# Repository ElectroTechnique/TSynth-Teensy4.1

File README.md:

# Teensy 4.1 based synthesizer using PJRC Audio Board and Audio Lib

Website: [electrotechnique.cc](https://electrotechnique.cc)

Front panel and Main PCB files are now available if you wan to get your own from a PCB facility like JLCPCB.

~~The pcb and front panel to build TSynth are available from [Tindie](https://www.tindie.com/products/electrotechnique/tsynth-teensy-based-diy-programmable-poly-synth/) with SMD 4067 multiplexers, 6N137 opto-isolator, capacitors and resistors fitted.~~ 

The entire cost of parts to build TSynth will be around $99 if you buy components from the cheaper suppliers and the build time around two hours to solder.
Plans for a 3D printed/laser cut enclosure are also available.

Questions: info@electrotechnique.cc

# Preset Patches
Format your SD card using [the SD Association formatter](https://www.sdcard.org/downloads/formatter/). Copy all the presets straight on to the card with no other files or folders.

# Instructions

The source code **requires** the latest Teensyduino from [PJRC](https://pjrc.com) to compile. You also need CircularBuffer from Agileware and Adafruit_GFX, which are available in the Arduino Library Manager.

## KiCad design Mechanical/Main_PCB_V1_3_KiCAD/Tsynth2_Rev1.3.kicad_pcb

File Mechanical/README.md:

- Electrical schematic
- 3D models - End cheeks, side panel columns, display standoff, encoder knob (D-shape shaft)

    EncoderKnobEC12_6mm is for 6mm splined encoder shafts
    
    EncoderKnobEC12_D_shape is for 6mm D-shaped encoder shafts

- Laser cutter plans - Sides and base

    T4_1_LaserCutCase3_5Jk.svg - Is for PCBs with 3.5mm headphone sockets
  
    T4_1_LaserCutCase6_35Jk.svg - Is for PCBs with 1/4" / 6.35mm headphone sockets
  
- BOM Excel file for ordering from Mouser

Fusion 360 models. These have internal dimensions for slots that are slightly bigger, to account for shrinkage of PLA plastic:
- [End Cheeks](https://a360.co/3azEESA)
- [Side Panel Column](https://a360.co/34T8akU)

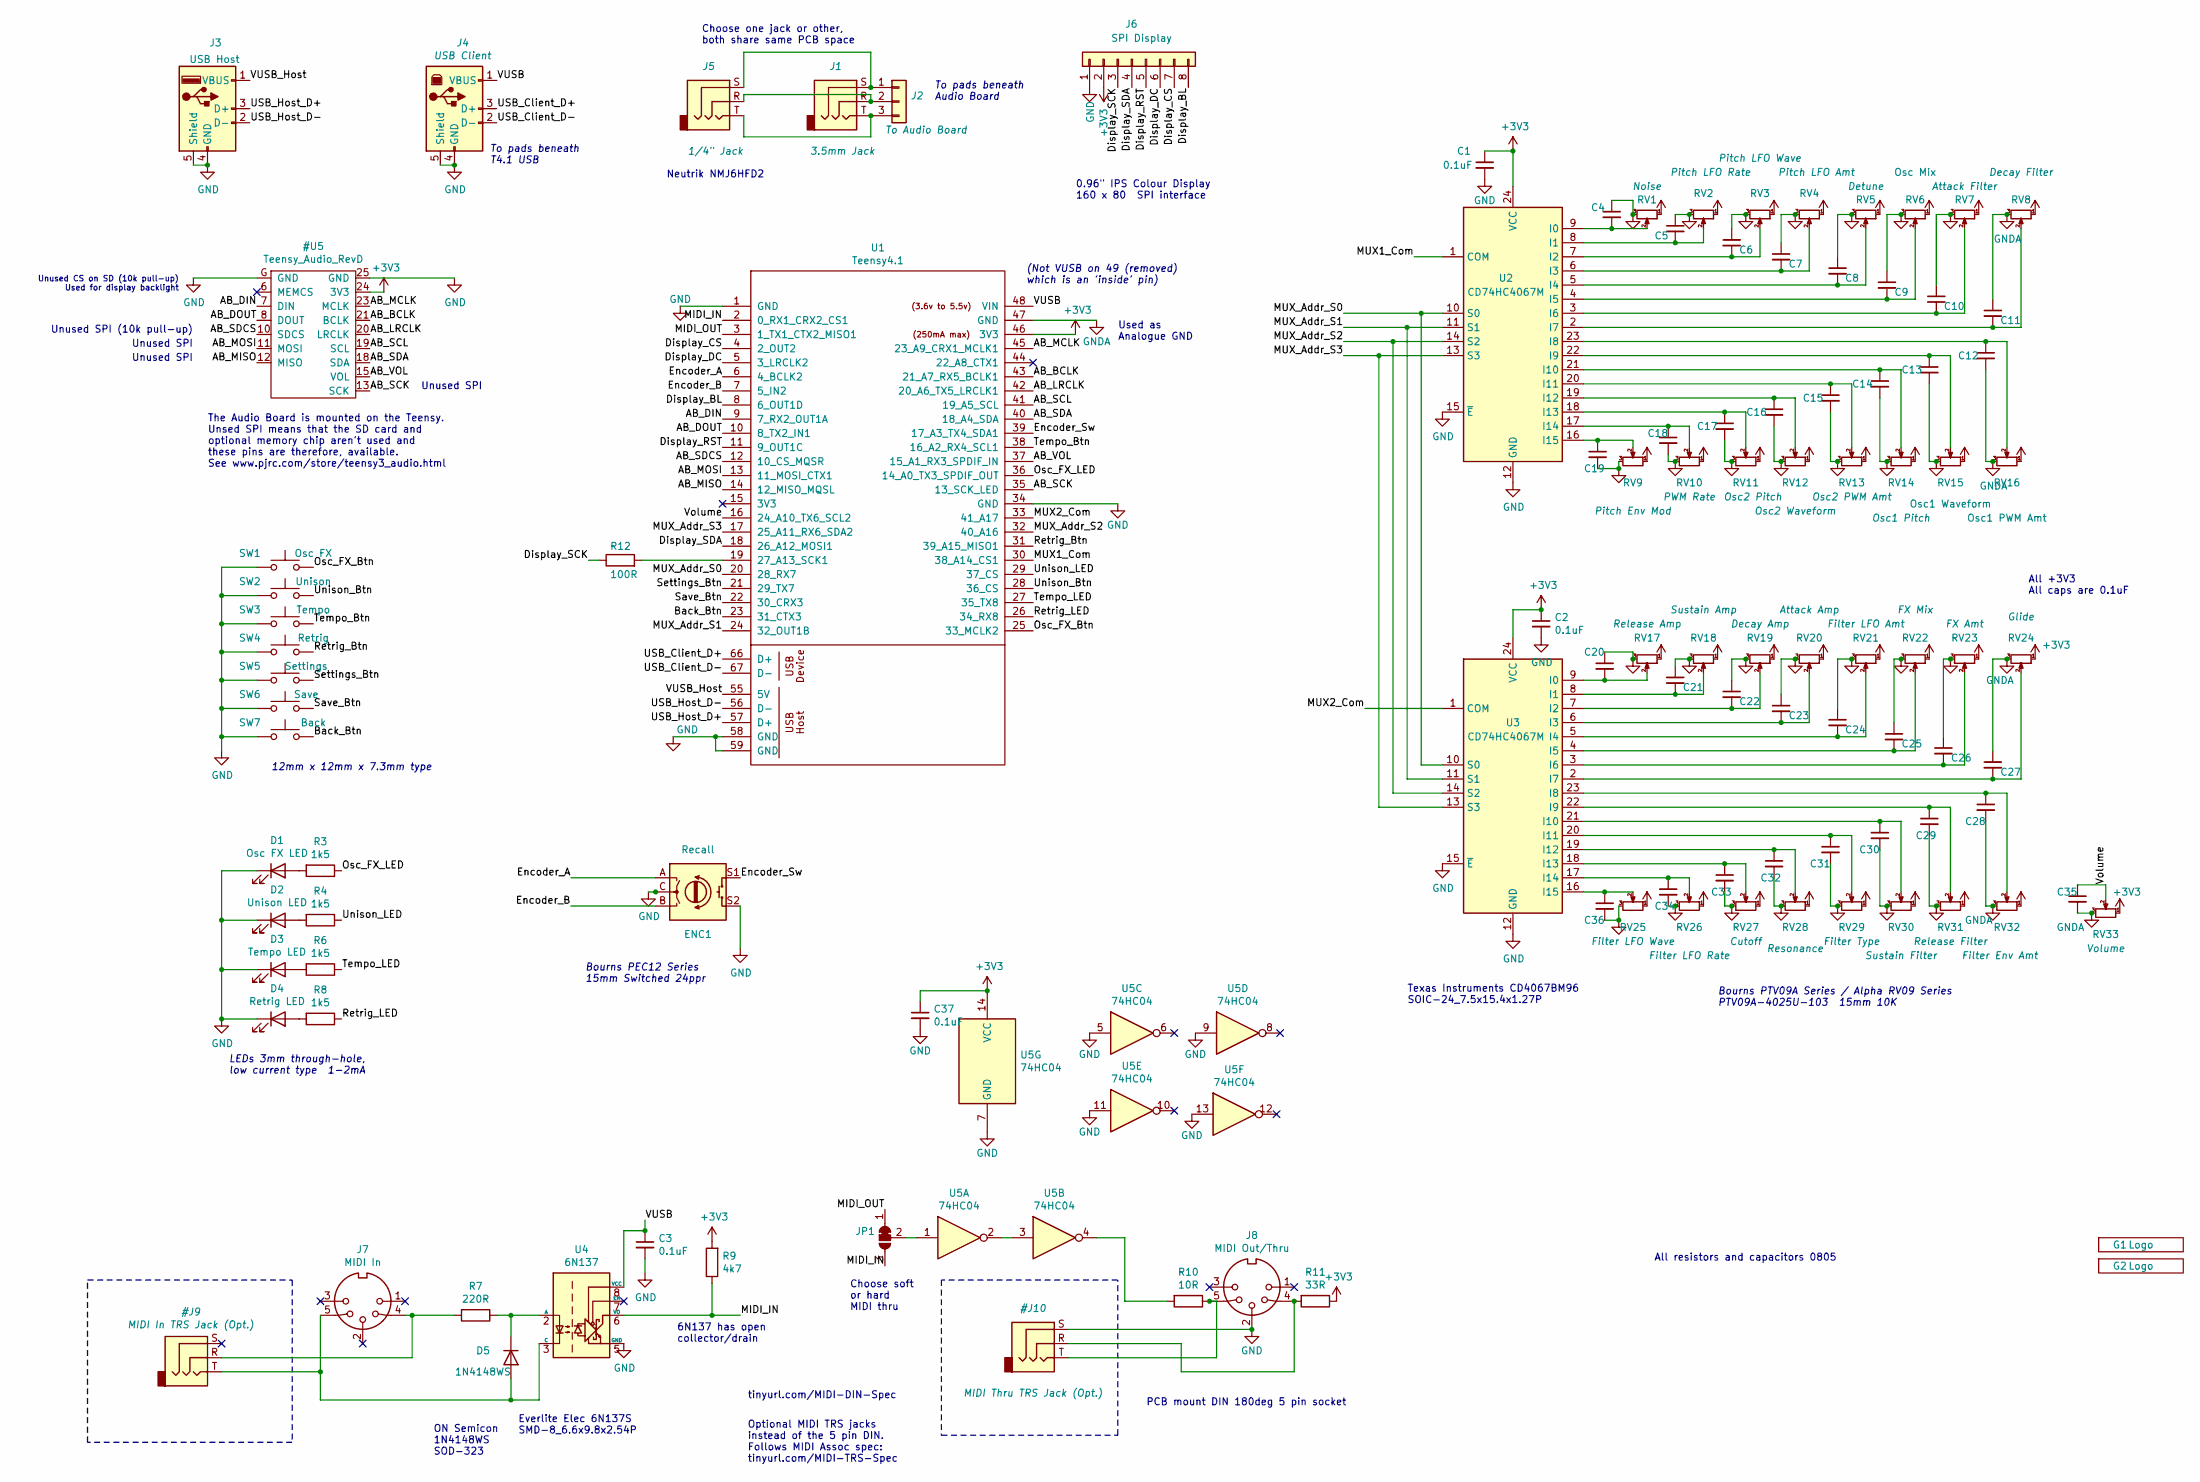
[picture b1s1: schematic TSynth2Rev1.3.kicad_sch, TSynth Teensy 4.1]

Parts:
C1, C37: 0.1uF; R_0805_2012Metric; LCSC C49678
C2, C3, C4, C5, C6, C7, C8, C9, C10, C11, C12, C13, C14, C15, C16, C17, C18, C19, C20, C21, C22, C23, C24, C25, C26, C27, C28, C29, C30, C31, C32, C33, C34, C35, C36: 0.1uF; R_0805_2012Metric
D1: Osc FX LED; LED_D3.0mm
D2: Unison LED; LED_D3.0mm
D3: Tempo LED; LED_D3.0mm
D4: Retrig LED; LED_D3.0mm
D5: 1N4148WS; D_SOD-323F; LCSC C2128
ENC1: Recall; RotaryEncoder_Alps_EC11E-Switch_Vertical_H20mm
G1, G2: Logo; TSynth PCB Logo 41mm
J1: 3.5mm Jack; Jack_3.5mm_Ledino_KB3SPRS_Horizontal
J2: To Audio Board; PinHeader_1x03_P2.54mm_Vertical
J3: USB Host; USB_A_Stewart_SS-52100-001_Horizontal
J4: USB Client; USB_B_OST_USB-B1HSxx_Horizontal
J5: 1/4" Jack; Jack_6.35mm_Neutrik_NMJ6HFD2_Horizontal
J6: SPI Display; PinHeader_1x08_P2.54mm_Vertical
J7: MIDI In; MIDI_DIN5
J8: MIDI Out/Thru; MIDI_DIN5
JP1: SolderJumper_3_Bridged12; SolderJumper-3_P1.3mm_Bridged12_RoundedPad1.0x1.5mm
R3, R4, R6, R8: 1k5; R_0805_2012Metric; LCSC C4310
R7: 220R; R_0805_2012Metric; LCSC C17557
R9: 4k7; R_0805_2012Metric; LCSC C17673
R10: 10R; R_0805_2012Metric; LCSC C17415
R11: 33R; R_0805_2012Metric; LCSC C17634
R12: 100R; R_0805_2012Metric; LCSC C17408
RV1: Noise; Potentiometer_Bourns_PTV09A-1_Single_Vertical
RV2: Pitch LFO Rate; Potentiometer_Bourns_PTV09A-1_Single_Vertical
RV3: Pitch LFO Wave; Potentiometer_Bourns_PTV09A-1_Single_Vertical
RV4: Pitch LFO Amt; Potentiometer_Bourns_PTV09A-1_Single_Vertical
RV5: Detune; Potentiometer_Bourns_PTV09A-1_Single_Vertical
RV6: Osc Mix; Potentiometer_Bourns_PTV09A-1_Single_Vertical
RV7: Attack Filter; Potentiometer_Bourns_PTV09A-1_Single_Vertical
RV8: Decay Filter; Potentiometer_Bourns_PTV09A-1_Single_Vertical
RV9: Pitch Env Mod; Potentiometer_Bourns_PTV09A-1_Single_Vertical
RV10: PWM Rate; Potentiometer_Bourns_PTV09A-1_Single_Vertical
RV11: Osc2 Pitch; Potentiometer_Bourns_PTV09A-1_Single_Vertical
RV12: Osc2 Waveform; Potentiometer_Bourns_PTV09A-1_Single_Vertical
RV13: Osc2 PWM Amt; Potentiometer_Bourns_PTV09A-1_Single_Vertical
RV14: Osc1 Pitch; Potentiometer_Bourns_PTV09A-1_Single_Vertical
RV15: Osc1 Waveform; Potentiometer_Bourns_PTV09A-1_Single_Vertical
RV16: Osc1 PWM Amt; Potentiometer_Bourns_PTV09A-1_Single_Vertical
RV17: Release Amp; Potentiometer_Bourns_PTV09A-1_Single_Vertical
RV18: Sustain Amp; Potentiometer_Bourns_PTV09A-1_Single_Vertical
RV19: Decay Amp; Potentiometer_Bourns_PTV09A-1_Single_Vertical
RV20: Attack Amp; Potentiometer_Bourns_PTV09A-1_Single_Vertical
RV21: Filter LFO Amt; Potentiometer_Bourns_PTV09A-1_Single_Vertical
RV22: FX Mix; Potentiometer_Bourns_PTV09A-1_Single_Vertical
RV23: FX Amt; Potentiometer_Bourns_PTV09A-1_Single_Vertical
RV24: Glide; Potentiometer_Bourns_PTV09A-1_Single_Vertical
RV25: Filter LFO Wave; Potentiometer_Bourns_PTV09A-1_Single_Vertical
RV26: Filter LFO Rate; Potentiometer_Bourns_PTV09A-1_Single_Vertical
RV27: Cutoff; Potentiometer_Bourns_PTV09A-1_Single_Vertical
RV28: Resonance; Potentiometer_Bourns_PTV09A-1_Single_Vertical
RV29: Filter Type; Potentiometer_Bourns_PTV09A-1_Single_Vertical
RV30: Sustain Filter; Potentiometer_Bourns_PTV09A-1_Single_Vertical
RV31: Release Filter; Potentiometer_Bourns_PTV09A-1_Single_Vertical
RV32: Filter Env Amt; Potentiometer_Bourns_PTV09A-1_Single_Vertical
RV33: Volume; Potentiometer_Bourns_PTV09A-1_Single_Vertical
SW1: Osc FX; SW_PUSH-12mm
SW2: Unison; SW_PUSH-12mm
SW3: Tempo; SW_PUSH-12mm
SW4: Retrig; SW_PUSH-12mm
SW5: Settings; SW_PUSH-12mm
SW6: Save; SW_PUSH-12mm
SW7: Back; SW_PUSH-12mm
U1: Teensy4.1; Teensy41
U2, U3: CD74HC4067M; SOIC-24W_7.5x15.4mm_P1.27mm; LCSC C496123
U4: 6N137; SMDIP-8_W9.53mm; LCSC C110020
U5: 74HC04; SOIC-14_3.9x8.7mm_P1.27mm; LCSC C5605

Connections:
/Back_Btn: SW7.2, U1.23 (31_CTX3)
/Display_BL: J6.8, U1.8 (6_OUT1D)
/Display_CS: J6.7, U1.4 (2_OUT2)
/Display_DC: J6.6, U1.5 (3_LRCLK2)
/Display_RST: J6.5, U1.11 (9_OUT1C)
/Display_SCK: J6.3, R12.1
/Display_SDA: J6.4, U1.18 (26_A12_MOSI1)
/Encoder_A: ENC1.A, U1.6 (4_BCLK2)
/Encoder_B: ENC1.B, U1.7 (5_IN2)
/Encoder_Sw: ENC1.S1, U1.39 (17_A3_TX4_SDA1)
/MIDI_IN: JP1.3 (B), R9.1, U1.2 (0_RX1_CRX2_CS1), U4.6 (VO)
/MIDI_OUT: JP1.1 (A), U1.3 (1_TX1_CTX2_MISO1)
/MUX1_Com: U1.30 (38_A14_CS1), U2.1 (COM)
/MUX2_Com: U1.33 (41_A17), U3.1 (COM)
/MUX_Addr_S0: U1.20 (28_RX7), U2.10 (S0), U3.10 (S0)
/MUX_Addr_S1: U1.24 (32_OUT1B), U2.11 (S1), U3.11 (S1)
/MUX_Addr_S2: U1.32 (40_A16), U2.14 (S2), U3.14 (S2)
/MUX_Addr_S3: U1.17 (25_A11_RX6_SDA2), U2.13 (S3), U3.13 (S3)
/Osc_FX_Btn: SW1.2, U1.25 (33_MCLK2)
/Osc_FX_LED: R3.1, U1.36 (14_A0_TX3_SPDIF_OUT)
/Retrig_Btn: SW4.2, U1.31 (39_A15_MISO1)
/Retrig_LED: R8.1, U1.26 (34_RX8)
/Save_Btn: SW6.2, U1.22 (30_CRX3)
/Settings_Btn: SW5.2, U1.21 (29_TX7)
/Tempo_Btn: SW3.2, U1.38 (16_A2_RX4_SCL1)
/Tempo_LED: R6.1, U1.27 (35_TX8)
/USB_Client_D+: J4.3 (D+), U1.66 (D+)
/USB_Client_D-: J4.2 (D-), U1.67 (D-)
/USB_Host_D+: J3.3 (D+), U1.57 (D+)
/USB_Host_D-: J3.2 (D-), U1.56 (D-)
/Unison_Btn: SW2.2, U1.28 (36_CS)
/Unison_LED: R4.1, U1.29 (37_CS)
/VUSB: C3.1, J4.1 (VBUS), U1.48 (VIN), U4.8 (VCC)
/VUSB_Host: J3.1 (VBUS), U1.55 (5V)
/Volume: C35.1, RV33.2, U1.16 (24_A10_TX6_SCL2)
GNDA: C4.1, C5.1, C6.1, C7.1, C8.1, C9.1, C10.1, C11.1, C12.2, C13.2, C14.2, C15.2, C16.2, C17.2, C18.2, C19.2, C20.1, C21.1, C22.1, C23.1, C24.1, C25.1, C26.1, C27.1, C28.2, C29.2, C30.2, C31.2, C32.2, C33.2, C34.2, C35.2, C36.2, RV1.3, RV2.3, RV3.3, RV4.3, RV5.3, RV6.3, RV7.3, RV8.3, RV9.3, RV10.3, RV11.3, RV12.3, RV13.3, RV14.3, RV15.3, RV16.3, RV17.3, RV18.3, RV19.3, RV20.3, RV21.3, RV22.3, RV23.3, RV24.3, RV25.3, RV26.3, RV27.3, RV28.3, RV29.3, RV30.3, RV31.3, RV32.3, RV33.3, U1.47 (GND)
unnamed: C4.2, RV1.2, U2.9 (I0)
unnamed: C5.2, RV2.2, U2.8 (I1)
unnamed: C6.2, RV3.2, U2.7 (I2)
unnamed: C7.2, RV4.2, U2.6 (I3)
unnamed: C8.2, RV5.2, U2.5 (I4)
unnamed: C9.2, RV6.2, U2.4 (I5)
unnamed: C10.2, RV7.2, U2.3 (I6)
unnamed: C11.2, RV8.2, U2.2 (I7)
unnamed: C12.1, RV16.2, U2.23 (I8)
unnamed: C13.1, RV15.2, U2.22 (I9)
unnamed: C14.1, RV14.2, U2.21 (I10)
unnamed: C15.1, RV13.2, U2.20 (I11)
unnamed: C16.1, RV12.2, U2.19 (I12)
unnamed: C17.1, RV11.2, U2.18 (I13)
unnamed: C18.1, RV10.2, U2.17 (I14)
unnamed: C19.1, RV9.2, U2.16 (I15)
unnamed: C20.2, RV17.2, U3.9 (I0)
unnamed: C21.2, RV18.2, U3.8 (I1)
unnamed: C22.2, RV19.2, U3.7 (I2)
unnamed: C23.2, RV20.2, U3.6 (I3)
unnamed: C24.2, RV21.2, U3.5 (I4)
unnamed: C25.2, RV22.2, U3.4 (I5)
unnamed: C26.2, RV23.2, U3.3 (I6)
unnamed: C27.2, RV24.2, U3.2 (I7)
unnamed: C28.1, RV32.2, U3.23 (I8)
unnamed: C29.1, RV31.2, U3.22 (I9)
unnamed: C30.1, RV30.2, U3.21 (I10)
unnamed: C31.1, RV29.2, U3.20 (I11)
unnamed: C32.1, RV28.2, U3.19 (I12)
unnamed: C33.1, RV27.2, U3.18 (I13)
unnamed: C34.1, RV26.2, U3.17 (I14)
unnamed: C36.1, RV25.2, U3.16 (I15)
unnamed: D1.2 (A), R3.2
unnamed: D2.2 (A), R4.2
unnamed: D3.2 (A), R6.2
unnamed: D4.2 (A), R8.2
unnamed: D5.1 (K), R7.1, U4.2 (A)
unnamed: J1.R, J2.2, J5.R
unnamed: J1.S, J2.1, J5.S
unnamed: J1.T, J2.3, J5.T
unnamed: JP1.2 (C), U5.1
unnamed: R10.2, U5.4
unnamed: R12.2, U1.19 (27_A13_SCK1)
unnamed: U5.2, U5.3

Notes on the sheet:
Bourns PTV09A Series / Alpha RV09 Series PTV09A-4025U-103 15mm 10K
6N137 has open collector/drain
Neutrik NMJ6HFD2
LEDs 3mm through-hole, low current type 1-2mA
Bourns PEC12 Series 15mm Switched 24ppr
Used as Analogue GND
Texas Instruments CD4067BM96 SOIC-24_7.5x15.4x1.27P
PCB mount DIN 180deg 5 pin socket
tinyurl.com/MIDI-DIN-Spec
(Not VUSB on 49 (removed) which is an 'inside' pin)
Unused SPI
Everlite Elec 6N137S SMD-8_6.6x9.8x2.54P
All +3V3 All caps are 0.1uF
Unused SPI (10k pull-up)
Optional MIDI TRS jacks instead of the 5 pin DIN. Follows MIDI Assoc spec: tinyurl.com/MIDI-TRS-Spec
ON Semicon 1N4148WS SOD-323
Choose soft or hard MIDI thru
All resistors and capacitors 0805
12mm x 12mm x 7.3mm type
The Audio Board is mounted on the Teensy. Unsed SPI means that the SD card and optional memory chip aren't used and these pins are therefore, available. See www.pjrc.com/store/teensy3_audio.html
To pads beneath T4.1 USB
0.96" IPS Colour Display 160 x 80 SPI interface
Choose one jack or other, both share same PCB space
Unused CS on SD (10k pull-up) Used for display backlight
To pads beneath Audio Board

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
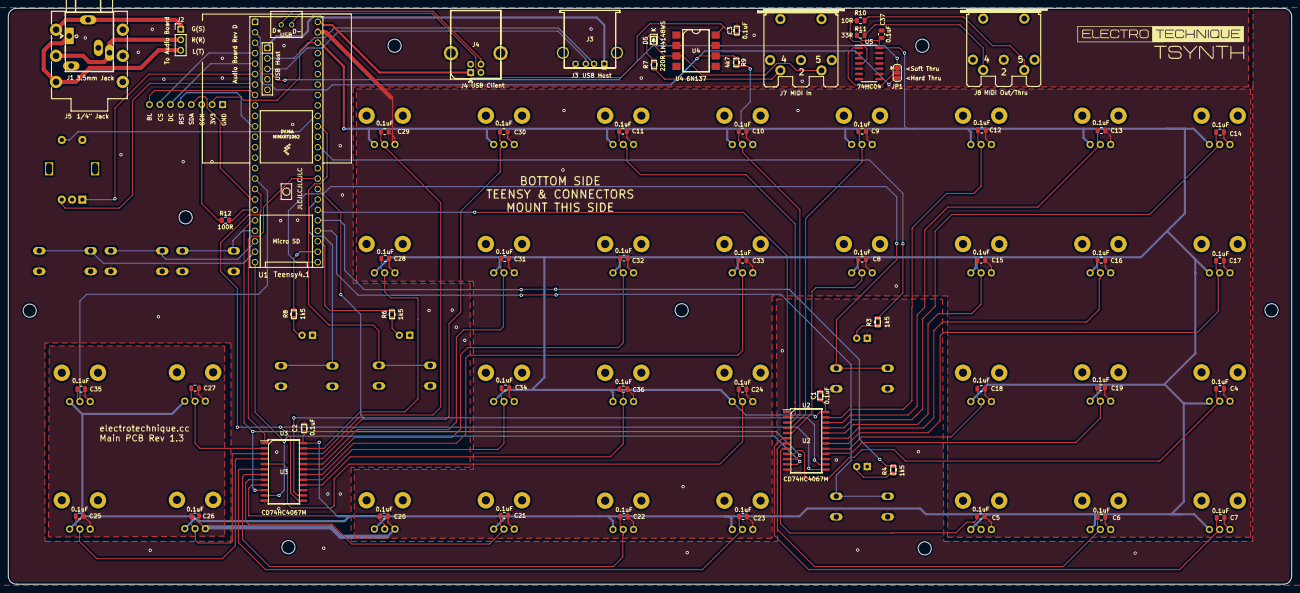
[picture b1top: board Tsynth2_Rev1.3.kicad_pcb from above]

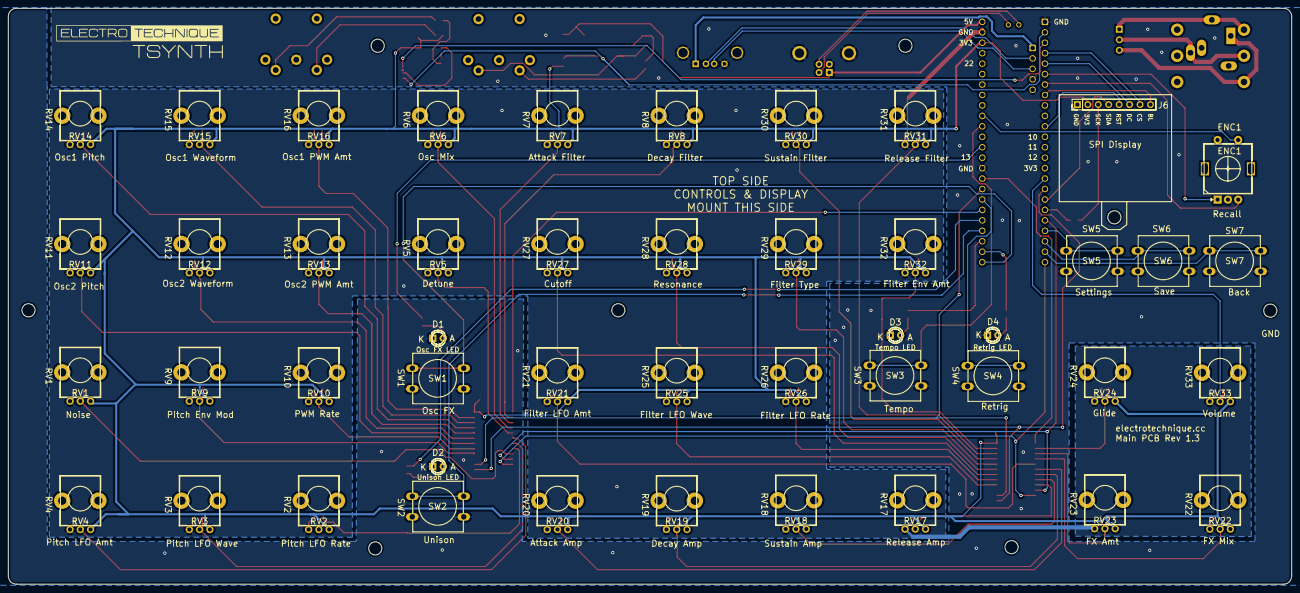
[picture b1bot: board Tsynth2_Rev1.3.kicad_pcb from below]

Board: 2 copper layers, 312.0 x 140.0 mm, 108 parts (47 on the bottom side), 86 nets.

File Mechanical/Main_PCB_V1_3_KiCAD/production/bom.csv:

Designator,Footprint,Quantity,Value,LCSC Part #
"C1, C10, C11, C12, C13, C14, C15, C16, C17, C18, C19, C2, C20, C21, C22, C23, C24, C25, C26, C27, C28, C29, C3, C30, C31, C32, C33, C34, C35, C36, C37, C4, C5, C6, C7, C8, C9",0805,37,0.1uF,
D1,LED_D3.0mm,1,Osc FX LED,
D2,LED_D3.0mm,1,Unison LED,
D3,LED_D3.0mm,1,Tempo LED,
D4,LED_D3.0mm,1,Retrig LED,
D5,D_SOD-323F,1,1N4148WS,
ENC1,RotaryEncoder_Alps_EC11E-Switch_Vertical_H20mm,1,Recall,
"G1, G2",TSynth PCB Logo 41mm,2,Logo,
J1,Jack_3.5mm_Ledino_KB3SPRS_Horizontal,1,3.5mm Jack,
J2,PinHeader_1x03_P2.54mm_Vertical,1,To Audio Board,
J3,USB_A_Stewart_SS-52100-001_Horizontal,1,USB Host,
J4,USB_B_OST_USB-B1HSxx_Horizontal,1,USB Client,
J5,Jack_6.35mm_Neutrik_NMJ6HFD2_Horizontal,1,"1/4"" Jack",
J6,PinHeader_1x08_P2.54mm_Vertical,1,SPI Display,
J7,MIDI_DIN5,1,MIDI In,
J8,MIDI_DIN5,1,MIDI Out/Thru,
R10,0805,1,10R,
R11,0805,1,33R,
R12,0805,1,100R,
"R3, R4, R6, R8",0805,4,1k5,
R7,0805,1,220R,
R9,0805,1,4k7,
RV1,Potentiometer_Bourns_PTV09A-1_Single_Vertical,1,Noise,
RV10,Potentiometer_Bourns_PTV09A-1_Single_Vertical,1,PWM Rate,
RV11,Potentiometer_Bourns_PTV09A-1_Single_Vertical,1,Osc2 Pitch,
RV12,Potentiometer_Bourns_PTV09A-1_Single_Vertical,1,Osc2 Waveform,
RV13,Potentiometer_Bourns_PTV09A-1_Single_Vertical,1,Osc2 PWM Amt,
RV14,Potentiometer_Bourns_PTV09A-1_Single_Vertical,1,Osc1 Pitch,
RV15,Potentiometer_Bourns_PTV09A-1_Single_Vertical,1,Osc1 Waveform,
RV16,Potentiometer_Bourns_PTV09A-1_Single_Vertical,1,Osc1 PWM Amt,
RV17,Potentiometer_Bourns_PTV09A-1_Single_Vertical,1,Release Amp,
RV18,Potentiometer_Bourns_PTV09A-1_Single_Vertical,1,Sustain Amp,
RV19,Potentiometer_Bourns_PTV09A-1_Single_Vertical,1,Decay Amp,
RV2,Potentiometer_Bourns_PTV09A-1_Single_Vertical,1,Pitch LFO Rate,
RV20,Potentiometer_Bourns_PTV09A-1_Single_Vertical,1,Attack Amp,
RV21,Potentiometer_Bourns_PTV09A-1_Single_Vertical,1,Filter LFO Amt,
RV22,Potentiometer_Bourns_PTV09A-1_Single_Vertical,1,FX Mix,
RV23,Potentiometer_Bourns_PTV09A-1_Single_Vertical,1,FX Amt,
RV24,Potentiometer_Bourns_PTV09A-1_Single_Vertical,1,Glide,
RV25,Potentiometer_Bourns_PTV09A-1_Single_Vertical,1,Filter LFO Wave,
RV26,Potentiometer_Bourns_PTV09A-1_Single_Vertical,1,Filter LFO Rate,
RV27,Potentiometer_Bourns_PTV09A-1_Single_Vertical,1,Cutoff,
RV28,Potentiometer_Bourns_PTV09A-1_Single_Vertical,1,Resonance,
RV29,Potentiometer_Bourns_PTV09A-1_Single_Vertical,1,Filter Type,
RV3,Potentiometer_Bourns_PTV09A-1_Single_Vertical,1,Pitch LFO Wave,
RV30,Potentiometer_Bourns_PTV09A-1_Single_Vertical,1,Sustain Filter,
RV31,Potentiometer_Bourns_PTV09A-1_Single_Vertical,1,Release Filter,
RV32,Potentiometer_Bourns_PTV09A-1_Single_Vertical,1,Filter Env Amt,
RV33,Potentiometer_Bourns_PTV09A-1_Single_Vertical,1,Volume,
RV4,Potentiometer_Bourns_PTV09A-1_Single_Vertical,1,Pitch LFO Amt,
RV5,Potentiometer_Bourns_PTV09A-1_Single_Vertical,1,Detune,
RV6,Potentiometer_Bourns_PTV09A-1_Single_Vertical,1,Osc Mix,
RV7,Potentiometer_Bourns_PTV09A-1_Single_Vertical,1,Attack Filter,
RV8,Potentiometer_Bourns_PTV09A-1_Single_Vertical,1,Decay Filter,
RV9,Potentiometer_Bourns_PTV09A-1_Single_Vertical,1,Pitch Env Mod,
SW1,SW_PUSH-12mm,1,Osc FX,
SW2,SW_PUSH-12mm,1,Unison,
SW3,SW_PUSH-12mm,1,Tempo,
SW4,SW_PUSH-12mm,1,Retrig,
SW5,SW_PUSH-12mm,1,Settings,
SW6,SW_PUSH-12mm,1,Save,
SW7,SW_PUSH-12mm,1,Back,
U1,Teensy41,1,Teensy4.1,
"U2, U3",SOIC-24W_7.5x15.4mm_P1.27mm,2,CD74HC4067M,
U4,SMDIP-8_W9.53mm,1,6N137,
U5,SOIC-14_3.9x8.7mm_P1.27mm,1,74HC04,

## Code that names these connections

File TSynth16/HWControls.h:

// This optional setting causes Encoder to use more optimized code,
// It must be defined before Encoder.h is included.
#define ENCODER_OPTIMIZE_INTERRUPTS
#include <Encoder.h>
#include <Bounce.h>

//Teensy 4.1 - Mux Pins
#define MUX_0 28
#define MUX_1 32
#define MUX_2 40
#define MUX_3 25
#define MUX1_S A14
#define MUX2_S A17
//Mux 1 Connections
#define MUX1_noiseLevel 0
#define MUX1_pitchLfoRate 1
#define MUX1_pitchLfoWaveform 2
#define MUX1_pitchLfoAmount 3
#define MUX1_detune 4
#define MUX1_oscMix 5
#define MUX1_filterAttack 6
#define MUX1_filterDecay 7
#define MUX1_pwmAmountA 8
#define MUX1_waveformA 9
#define MUX1_pitchA 10
#define MUX1_pwmAmountB 11
#define MUX1_waveformB 12
#define MUX1_pitchB 13
#define MUX1_pwmRate 14
#define MUX1_pitchEnv 15
//Mux 2 Connections
#define MUX2_release 0
#define MUX2_sustain 1
#define MUX2_decay 2
#define MUX2_attack 3
#define MUX2_filterLFOAmount 4
#define MUX2_FXMix 5
#define MUX2_FXAmount 6
#define MUX2_glide 7
#define MUX2_filterEnv 8
#define MUX2_filterRelease 9
#define MUX2_filterSustain 10
#define MUX2_filterType 11
#define MUX2_resonance 12
#define MUX2_cutoff 13
#define MUX2_filterLFORate 14
#define MUX2_filterLFOWaveform 15

//Teensy 4.1 Pins
#define OSC_FX_SW 33
#define FILTER_LFO_RETRIG_SW 39
#define UNISON_SW 36
#define TEMPO_SW 16
#define RECALL_SW 17
#define SAVE_SW 30
#define SETTINGS_SW 29
#define BACK_SW 31
#define VOLUME_POT A10

#define ENCODER_PINA 4
#define ENCODER_PINB 5

#define RETRIG_LED 34
#define TEMPO_LED 35
#define UNISON_LED 37
#define OSC_FX_LED 14

#define MUXCHANNELS 16
#define QUANTISE_FACTOR 7

#define DEBOUNCE 30

static byte muxInput = 0;
static int mux1ValuesPrev[MUXCHANNELS] = {};
static int mux2ValuesPrev[MUXCHANNELS] = {};

static int mux1Read = 0;
static int mux2Read = 0;
static int volumeRead = 0;
static int volumePrevious = 0;
static long encPrevious = 0;

//These are pushbuttons and require debouncing
Bounce oscFXSwitch = Bounce(OSC_FX_SW, DEBOUNCE);
Bounce filterLFORetrigSwitch = Bounce(FILTER_LFO_RETRIG_SW, DEBOUNCE);
Bounce unisonSwitch = Bounce(UNISON_SW, DEBOUNCE);
Bounce tempoSwitch = Bounce(TEMPO_SW, DEBOUNCE);

Bounce recallButton = Bounce(RECALL_SW, DEBOUNCE); //On encoder
boolean recall = true; //Hack for recall button
Bounce saveButton = Bounce(SAVE_SW, DEBOUNCE);
boolean del = false; //Hack for save button
Bounce settingsButton = Bounce(SETTINGS_SW, DEBOUNCE);
boolean reini = false; //Hack for settings button
Bounce backButton = Bounce(BACK_SW, DEBOUNCE);
boolean panic = false; //Hack for back button
Encoder encoder(ENCODER_PINB, ENCODER_PINA);//This often needs the pins swapping depending on the encoder

void setupHardware()
{
  //Mux address pins
  pinMode(MUX_0, OUTPUT);
  pinMode(MUX_1, OUTPUT);
  pinMode(MUX_2, OUTPUT);
  pinMode(MUX_3, OUTPUT);

  //Mux ADC
  pinMode(MUX1_S, INPUT);
  pinMode(MUX2_S, INPUT);

  //Volume ADC
  pinMode(VOLUME_POT, INPUT);

  //Switches
  pinMode(OSC_FX_SW, INPUT_PULLUP);
  pinMode(FILTER_LFO_RETRIG_SW, INPUT_PULLUP);
  pinMode(UNISON_SW, INPUT_PULLUP);
  pinMode(TEMPO_SW, INPUT_PULLUP);
  pinMode(RECALL_SW, INPUT_PULLUP); //On encoder
  pinMode(SAVE_SW, INPUT_PULLUP);
  pinMode(SETTINGS_SW, INPUT_PULLUP);
  pinMode(BACK_SW, INPUT_PULLUP);

  //LEDs
  pinMode(RETRIG_LED, OUTPUT);
  pinMode(TEMPO_LED, OUTPUT);
  pinMode(UNISON_LED, OUTPUT);
  pinMode(OSC_FX_LED, OUTPUT);
}

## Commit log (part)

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2020-07-23 Updated to use band-limited waveforms
2020-08-13 Add Velocity sensitivity
2020-08-13 Add velocity curves
2020-09-24 V2.00 - First release
2020-10-18 V2.01 - Mod wheel level adds to osc LFO level.
2020-11-15 V2.02 - Volume control, unison voice level and oscilloscope
    Volume control reverted back to controlling only headphone volume. USB digital and line out are at fixed volumes.
    Fix to code that sets the volume level due to velocity that made unison voices too loud.
    Some improvement to oscilloscope display.
2020-11-30 V2.03 - Fixed reinitialise problem caused between RE_READ and QUANTISE_FACTOR
2020-11-30 V2.03 - Fixed reintialise problem cause by RE_READ and QUANTISE_FACTOR
2021-01-12 V2.10 - Support for V1.3 PCB - soft MIDI thru, normalised unison volume level
2021-01-12 Support V1.3 PCB
2021-01-12 V2.10 - Support for V1.3 PCB - Soft MIDI thru/out, normalise unison volume levels
2021-03-06 Fix all compilation warnings, favor strict & cross-platform compatible casts.
2021-03-06 Fix visual audio design graph not showing custom classes, now works while preserving local classes redefintions.
2021-03-06 Add Side Panel Column Stl and freecad models variants for plastic (larger) studs.
2021-03-06 Reorganize and sort AudioPatching.h
2021-03-06 Clean up most of the x.y coordinates in the full design for better visual inspection in the Teensy Audio System Design Tool.
2021-03-06 Cleanup usbAudio x coordinate decimals.
2021-04-06 Fixed minor bugs with parameter save and recall. Richer stereo chorus.
2021-04-06 V2.11 - Fixed minor bugs with parameter save and recall. Richer stereo chorus.
2021-04-11 V2.12 - Stereo chorus improvement
2021-04-11 V2.12 - Stereo chorus improvements
2021-04-11 Support platformio.
2021-04-13 Update voice code to use Oscillator array.
2021-04-13 Use Oscillator array for other updates.
2021-04-13 More usage of the oscillator array.
2021-04-13 Additional fixes
    Added sixth phase tap
    Corrected lfoIndex 1-6 values to properly represent 6 phases at 60 degree intervals
    Corrected index cut/paste errors in waveform summation code
2021-04-13 Additional fixes
    Added definitions for index variables to support sixth phase tap
2021-04-14 V2.13 - Stereo Chorus - improvements and bugfixes
2021-04-14 - V2.14 - C&P error on updateAttack
2021-04-14 V2.14 - Stereo Chorus - improvements and bugfixes (and fix C&P error on updateAttack)
2021-04-17 Fix unison voice mixer level.
2021-04-17 - V2.15 - Update version number.
2021-04-17 V2.15 - Stereo Chorus - improvements and bugfixes (and fix C&P error on updateAttack and Unison voice levels)
2021-04-17 Voice object encapsulating the patch and state of one voice.
    Use uint8_t because the other variables do.
2021-04-17 Use VoiceGroup.
    Move unison support into VoiceGroup.
    Fix the mixer level.
    Avoid range based for loop.
    Remove some unused stuff.
2021-04-18 Monophonic mode.
2021-04-18 Add monophonic mode note priorities.
    Disable legato.
2021-04-18 Fix detune knob responsiveness during note.
2021-04-18 Fix glide.
2021-04-19 Fix problems with selecting settings and order of Monophonic mode to match indexes
2021-04-19 Fix problems with selecting settings - end of value list
2021-04-19 Move remaining note parameters away from globals.
2021-04-19 Move more patch configuration parameters into the VoiceGroup.
2021-04-19 Move pitch envelope to voice group.
2021-04-19 Move PWM values into VoiceGroup
2021-04-20 Move Osc Mix and FX state to voice group.
2021-04-20 Move cutoff to voice group.
2021-04-20 Move resonance and filter mix to voice group.
2021-04-20 Move filter envelope to voice group.
2021-04-21 Fix voice initialize.
2021-04-21 Move filter and amp ADSR to voice group.
2021-04-21 Cleanup some leftover stuff.
2021-04-22 Sustain should use LINEAR[value]
2021-04-22 Minor cleanup.
    Remove some magic numbers.
    Functions for repeated operations.
2021-04-23 12 copies of filterLfo, move filterLfo into VoiceGroup.
2021-04-23 Copy of pwmLfo A and B per voice.
2021-04-23 Split noise mixer per voice and move to voice group.
2021-04-23 Split pwa and pwb for each voice.
2021-04-24 Synchronize LFO in voice group.
2021-04-25 Use dynamic audio connections in voice groups.
2021-04-25 Share a single noise mixer per voice group.
2021-04-25 FilterLFO to dynamic audio connection.
2021-04-25 PWM LFO to dynamic connection in voice group, re-enable filter LFO.
2021-04-25 Dynamic patching with pitch filters, they still need to be moved into the VoiceGroup.
2021-04-25 Move pitch mixers into voice group.
2021-04-26 CCpitchA was lost!
2021-04-27 Way hey, pitchbend's back! Quite easy too.
2021-04-27 Move mono mode to a patch setting.
2021-04-28 Fix amp env display paramtype (C&P error)
2021-04-29 Update line endings and git line ending config.
2021-04-30 Hack together multiple voice groups prototype.
2021-04-30 Multiple timber prototype.
2021-04-30 Fix some rebase errors.
2021-04-30 Reorder some audio connections.
2021-05-01 first commit for exponential envelope.
2021-05-01 added hex file
2021-05-03 More dynamic audio patching.h
2021-05-04 Fixed EEPROM store and recall for envelope types
2021-05-04 Updated some comments
2021-05-04 Fix audio object creation order.
2021-05-04 Remove more old stuff.
2021-05-05 Make things more dynamic. Things don't sound right anymore.
    Move effect mixer into the voice group. The code is pretty nice now but things don't sound right anymore.
2021-05-05 Added release bias so it shuts off earlier
2021-05-06 Missing )
2021-05-06 Route effect mixer.
2021-05-07 forked the TSynth branch
2021-05-07 merged in fast sustain
2021-05-08 Changed from unsigned to signed integers in envelope filters, cleaned up code and comments
2021-05-09 Proper recall of EEPROM env type at start-up
2021-05-10 Rearrange Settings menu items, bugfix to patchname in serial monitor
2021-05-10 Firmware V2.20
2021-05-10 Dynamic initialization
2021-05-10 Move local audio connections into the structs.
2021-05-11 Move global audio objects into a struct.
2021-05-11 Revert "Update line endings and git line ending config."
    This reverts commit d68331e927c5a5f00579f1de91431351d1e772b4.
2021-05-11 V2.20 firmware
2021-05-11 Tidy code for release
2021-05-11 V2.20 - Monophonic mode, exponential envelopes
2021-05-12 Remove debugging code
2021-05-13 Fix filter LFO.
2021-05-13 Helper functions for dynamic patching.
2021-05-13 Lower VOICEMIXERLEVEL from 0.35 to 0.25 as we were getting distortion on preset 40.
2021-05-13 Fix X Mod.
2021-05-14 Fix white noise.
2021-05-15 Reduce AudioMemory to 58
2021-05-16 Mix ensemble effects per timber.
2021-05-16 Move effect mixer into voice group.
2021-05-16 Fix gain, no need to apply mixerLevel twice.
2021-05-16 Improved unison logic.
    1. The voice now includes enough metadata that the display doesn't need
    knowledge of unison logic.
    2. Display now maintains the note border even while note is playing.
    3. Display rectangle is now always visible to allow differentiating between
    different timbres.
    4. Improved unison note selection:
2021-05-17 Store glide shape
2021-05-17 Increase settings no.
2021-05-17 Prototype that puts 6 voices on channel 1 and the rest on the other channels.
2021-05-17 Change DC objects in patching
2021-05-18 Fix setMode() change over
2021-05-18 Dynamic number of voices.
2021-05-19 Change Unison and OscFX buttons to cycle through options
2021-05-19 Revert "Master+mt --> Master+MT+ExpGlide"
2021-05-19 OscFX and Unison Buttons cycle through options
2021-05-19 OscFX & Unison buttons cycle through options
2021-05-20 New button class to help detect different activation types.
2021-05-21 Add TButton class
2021-05-21 Added Exp Glide
2021-05-21 updated exponential glide to current
2021-05-22 Fix OscFX changing Osc Mix levels back correctly when turned off. Plus some comments.
2021-05-22 Attempting to improve volume level again.
2021-05-22 Move monophonic priorities to a class.
2021-05-22 Search for MonoNoteHistory #include, in directory
2021-05-26 Handle noteOff() states
2021-05-27 Added and updated for recent env changes
2021-05-27 Changed notOn and noteOff to a switch block and increased speed of forced release by x8
2021-05-28 Changed force release factor from 8 to 4. This is value may change later or be replaced with a linear segment.
2021-05-29 Use a fixed array for mono note history.
    Add a unit test for the new case where push drops the oldest element.
2021-05-31 Adjusted forced release K and bias for ~5ms between forced release and next attack.
2021-06-01 Pulled latest Master+MT
2021-06-01 Cleaned up unused test code. Added code to catch states not used in linear envelope mode if in such state when switching to linear mode.
2021-06-03 Improve resonance range
    Solved problem where resonance values below 1.1 caused noise https://forum.pjrc.com/threads/67358-AudioFilterStateVariable-unwanted-noise
2021-06-04 Improve resonance range.
2021-06-04 V2.21 - Improve resonance range
2021-06-06 New SettingsService
2021-06-06 Make sure current menu setting is reloaded when patch is changed.
2021-06-07 Reconnect the scope and peak audio objects.
2021-06-08 Decouple globals.
2021-06-20 V2.30 - Exponential Glide option. Major refactoring of source code.
2021-06-20 V2.30 Firmware - exponential Glide option.
2021-06-20 V2.30 - Exponential Glide option.
2021-07-02 V2.31 - Fixed crash on unison with monophonic
2021-07-05 Now included in TD1.54
2021-07-22 Added troubleshooting section
2021-10-10 Use Windows line endings everywhere.
2021-10-10 Add .gitattributes
2021-10-19 Option to disable audio interface.
2021-10-19 Split EepromMgr.h
2021-10-19 Split ST7735Display.h
2021-10-19 Add unit tests.
2021-10-19 Refactor settings to support multiple menus.
2021-10-19 Move some constants out of VoiceGroup.
2021-10-19 Split PatchMgr.h
2021-10-19 Split VoiceGroup.h
2021-10-19 Split Settings.h
2021-10-19 Fix indent.
2021-10-19 Split Voice.h
2021-10-19 Split Oscilloscope.h
2021-10-19 Experimenting.
2021-10-20 WIP: hard coded 3 timbres.
2021-10-21 WIP: reorganizing voices seems to work. Change note on color to use the group color.
2021-10-29 Multi-timbre menu working - hard coded values for now.
2021-10-30 Add UI for configuring timbres list.
2021-10-31 WIP towards loading MT from config.
2021-10-31 Decouple with a function pointer.
2021-11-03 Multiple patches, loaded by name, configurable.
2021-11-03 Code cleanup.
2021-11-04 Fix header file refs.
2022-01-05 V2.32 Fix PW amount for Osc 2 not updated from patch.
2022-01-05 Fixed PW amount on Osc 2 not updated from patch
2022-01-09 Add new Oscilloscope
2022-03-03 Improve RAM usage - smaller ints
2022-03-04 RAM memory improvements & larger MIDI buffer
2022-03-29 V2.33 - Oscilloscope and memory improvement, exp amp and filter env defaults
2022-03-29 V2.33 - Oscilloscope and memory improvements, exp ap and filter shape defaults.
2023-11-20 V2.35 - Improvements to handling of USB host plugging in, SPI speed dropped for lower noise, loop() improvement
2023-11-20 V2.35
2023-12-25 V2.36 - Fix first held voice silenced - issue #136
    V2.36 - Fix first held voice silenced - issue #136
2024-08-19 Dummy commit
    For some reason identical files are showing as every line deleted and re-created
2024-08-19 Fix issue with exponential envelope with non-zero delay
    In a corner case, where the state becomes STATE_IDLE EXACTLY at the end of an update(), AND noteOn() is called before the next update() occurs, AND delay_count is non-zero, AND the exponential envelo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
